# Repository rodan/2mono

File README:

small circuit that controls a APC SMART ups remotely via an Intertechno [1] relay. files are compatible with Eagle CAD 6.0+.

author:	 Petre Rodan <2b4eda@subdimension.ro>
version: rev1
license: GPLv3

the ups has two different buttons for power-on and off, and they need to be pushed at least a few seconds to activate. a single RF relay [1] will provide input to the board where edge triggering and two monostables and will control 2 small reed relays linked in parallel with the UPS buttons.

the board and the rf relay fit behind the plastic front pannel of the ups. see some pictures of the setup here [4].

tested with
 APC Smart-UPS 1000VA USB & Serial 230V (sku sua1000i) [2]
 APC Smart-UPS 1500VA USB & Serial 230V (sku sua1500i) [3]

[1] http://www.intertechno.at/produkte/empfaenger/schalter/CMR-1224.html
[2] http://www.apc.com/resource/include/techspec_index.cfm?base_sku=sua1000i
[3] http://www.apc.com/resource/include/techspec_index.cfm?base_sku=sua1500i
[4] https://photos.app.goo.gl/6eNyjTDTvezkR9XZ8

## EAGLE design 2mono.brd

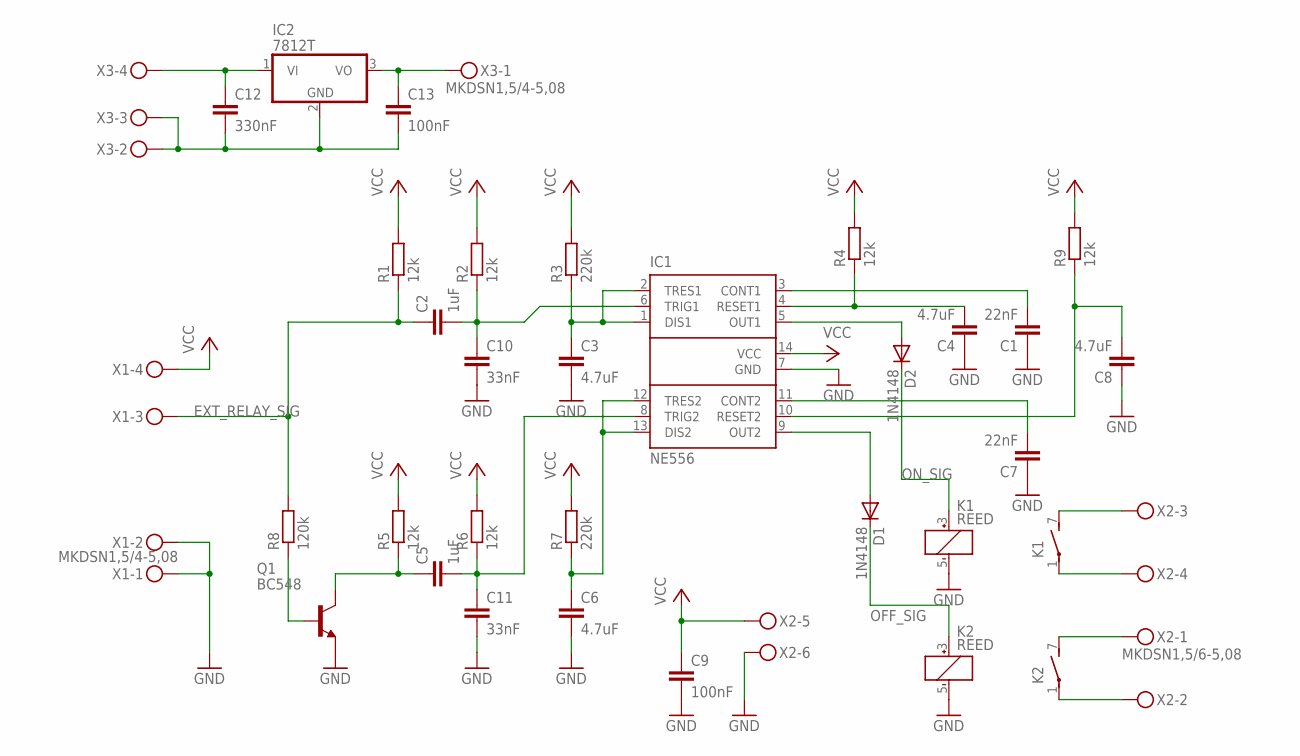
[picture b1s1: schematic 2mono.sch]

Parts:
C1, C7: 22nF; C050-025X075
C2, C5: 1uF; C025-030X050
C3, C4, C6, C8: 4.7uF; C025-030X050
C9, C13: 100nF; C075-042X103
C10, C11: 33nF; C050-030X075
C12: 330nF; C075-032X103
D1, D2: 1N4148; DO35-10
IC1: NE556; DIL14
IC2: 7812T; TO220H
K1, K2: REED
Q1: BC548; TO92-EBC
R1, R2, R4, R5, R6, R9: 12k; 0207/12
R3, R7: 220k; 0207/12
R8: 120k; 0207/12
X1, X3: MKDSN1,5/4-5,08
X2: MKDSN1,5/6-5,08

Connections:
EXT_RELAY_SIG: C2.1, R1.1, R8.2, X1.3
GND: C1.1, C3.2, C4.1, C6.2, C7.1, C8.1, C9.2, C10.2, C11.2, IC1.7 (GND), K1.5 (-), K2.5 (-), Q1.E, X1.1, X1.2, X2.6
unnamed: C3.1, IC1.1 (DIS1), IC1.2 (TRES1), R3.1
unnamed: C2.2, C10.1, IC1.6 (TRIG1), R2.1
unnamed: C6.1, IC1.12 (TRES2), IC1.13 (DIS2), R7.1
unnamed: C1.2, IC1.3 (CONT1)
unnamed: C4.2, IC1.4 (RESET1), R4.1
unnamed: C5.1, Q1.C, R5.1
unnamed: Q1.B, R8.1
unnamed: C5.2, C11.1, IC1.8 (TRIG2), R6.1
unnamed: C7.2, IC1.11 (CONT2)
unnamed: C8.2, IC1.10 (RESET2), R9.1
unnamed: D2.A, IC1.5 (OUT1)
unnamed: K2.7 (S), X2.1
unnamed: K2.1, X2.2
unnamed: K1.1, X2.4
unnamed: D1.A, IC1.9 (OUT2)
unnamed: C12.1, IC2.1 (VI), X3.4
unnamed: K1.7 (S), X2.3
unnamed: C13.1, IC2.3 (VO), X3.1
unnamed: C12.2, C13.2, IC2.2 (GND), X3.2, X3.3
OFF_SIG: D1.C, K2.3 (+)
ON_SIG: D2.C, K1.3 (+)
VCC: C9.1, IC1.14 (VCC), R1.2, R2.2, R3.2, R4.2, R5.2, R6.2, R7.2, R9.2, X1.4, X2.5

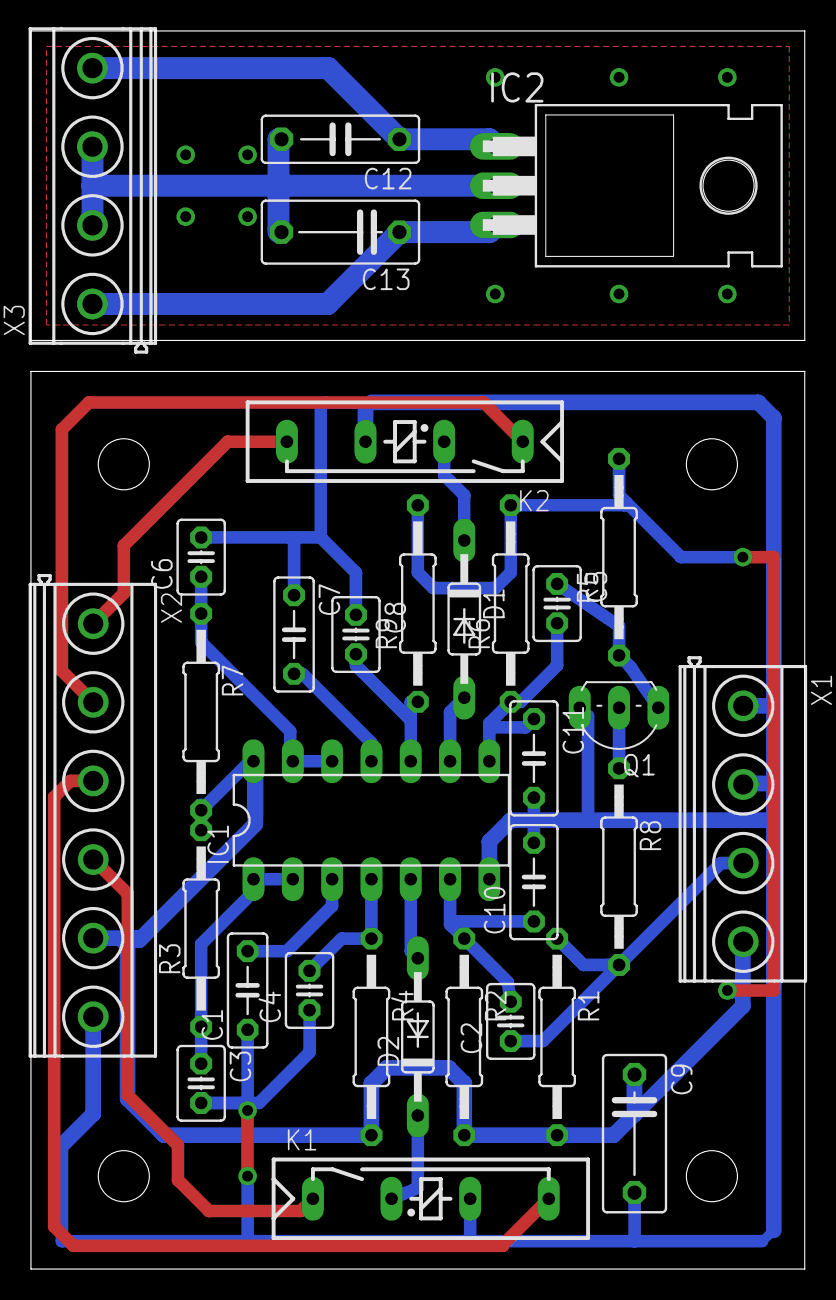
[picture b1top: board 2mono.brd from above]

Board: 2 copper layers, 50.0 x 80.0 mm, 32 parts (0 on the bottom side), 24 nets.

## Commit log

2012-02-18 initial import
2012-03-06 pictures\!
2018-09-01 email change
2021-10-02 update photo album link
